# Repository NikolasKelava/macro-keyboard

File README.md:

# Macro Keyboard

A custom, wireless **Bluetooth LE macro keypad** with 12 mechanical keys, a magnetic rotary
encoder, and a 128×64 OLED built on a Nordic **nRF52840** module and running
[**ZMK**](https://zmk.dev). Keys and profiles are configurable live over ZMK
Studio; the encoder is a per-profile knob (volume / vertical scroll / horizontal
scroll / browser tabs). Battery-powered (2000 mAh LiPo) with USB-C charging.

This project was submitted to the **Hack Club Horizons** program. Its progress is logged
in [JOURNAL.md](./JOURNAL.md). The admission is still pending.

---

## What is a macro keyboard?

A macro keyboard is a **Human Interface Device** (HID), which executes **macros** on a connected
host computer. In this sense, it functions like a conventional keyboard, serving as the 
interface between human input and a computer action.

The difference between a standard keyboard and a macro keyboard lies in their respective 
functionalities. A standard keyboard performs "normal" key bindings (e.g., numbers, letters,
and function buttons), while a macro keyboard performs macros. These can be media keys 
(e.g., volume up/down, skip title), open applications on the host computer or executing 
entire commands, performing actions that would otherwise require **multiple keystrokes on a 
standard keyboard**.

This makes it easier to navigate the operating system by **removing friction** between the user
and the host.

## What is my macro keyboard and what does it do?

**My macro keyboard has 12 macro keys, a rotary magnetic encoder, an OLED display, is battery 
powered and supports up to 7 profiles.**

The **macro assigned to each key** can be configured **per profile**. Depending on which profile is 
active, a key can have up to seven different functions. Consequently, we can perform up to **84
different actions** with our 12 keys.

The **encoder mode** can also be configured. It can act as a **scroll wheel** in both vertical and
horizontal direction, control the **volume** or switch between browser tabs on the host. These **modes 
are bound to each profile** and can be changed by assigning a key on a profile, that cycles through 
the modes of the encoder. When moving to the next keypad profile, the encoder mode changes to the 
active profile's encoder mode. Returning to the previous profile will revert the encoder mode to its 
previous state.

The **OLED display** shows the selected keypad profile, the battery capacity, the connection mode, and 
the encoder mode.

You can think of the keypad profiles as the **user layer** of the macro keypad. These profiles are 
called the "keymap", and they are the layers where the macro keyboard's functionality is configured. 
This user layer live directly on the macro keyboard, so the macros stay **the same even when changing 
host devices.** A **profile** button on the macro keyboard is used to switch between profiles.

You can **configure** the keymap and profiles in real time without recompiling or reflashing the keypad 
through [**ZMK Studio**](https://zmk.studio), a graphical user interface for ZMK keyboard firmware.

The macro keyboard connects as a keypad **via Bluetooth** or **USB**. Hosts are cross-platform (Windows, 
macOS, Linux, and iOS). The keypad can be paired with up to five hosts and conveniently switch 
between them via assigned keys on the keymap.

## Layout

## Demo & photos

### Demo video:

[Quick demo video on youtube](https://youtube.com/shorts/6OSJ7Yoke_U)
 
### Photos: 

## Hardware overview

| | |
|---|---|
| **MCU** | Raytac MDBT50Q-1MV2 (nRF52840 Module) |
| **Input** | 12-key matrix with mx switches (3 rows × 4 cols) + 1 profile button |
| **Encoder** | AMS AS5600 magnetic rotary encoder (over I2C) |
| **Display** | 128×64 SSD1306 OLED (over I2C, with 1 bpp) |
| **Power** | 2000 mAh LiPo, BQ24040 charger, USB-C |
| **Enclosure** | 3D printed |

## Firmware overview

The macro keyboard runs custom ZMK Firmware, configured and built over a local toolchain.
> "ZMK Firmware is an open source (MIT) keyboard firmware built on the Zephyr™ Project Real Time Operating System (RTOS)." ([Introduction to ZMK](https://zmk.dev/docs))

Full toolchain and architecture notes are in [firmware/CLAUDE.md](./firmware/CLAUDE.md).

## Repository layout

```
macro_keyboard/
├── README.md               ← you are here
├── JOURNAL.md              ← build devlog
├── assets/journal-assets/  ← images referenced from the journal
├── firmware/
│   ├── CLAUDE.md               full firmware architecture & build notes
│   ├── IMPLEMENTATION_PLAN.md  milestone-by-milestone history
│   ├── zmk-config/             ZMK config: custom board files, module, 
│   │                           AS5600 driver, behaviors
│   └── zmk                     ZMK submodule (ZMK version for my toolchain)
└── hardware/
    ├── BOM.csv          build BOM
    ├── BOM_PCB.csv      per-component board BOM (JLCPCB SMT + hand-soldered)
    ├── BUILD.md         full build and assembly guide to reproduce the macro keyboard
    ├── PCB/KiCad/Macro-Keyboard-v4/   schematic, board, Gerbers, KiCad design files
    └── CASE/                          3D-printed enclosure (Fusion + mesh exports)
```

## Bill of Materials

- **[hardware/BOM.csv](./hardware/BOM.csv)** — **Master/build cost BOM**:
  PCB fabrication, JLCPCB assembly (the parts JLC populates), shipping, the on-PCB parts I 
  solder myself (OLED, key switches, JST, SWD header), and all off-PCB parts (encoder bearing/
  magnet/knob, battery, keycaps, enclosure, screws) with the approximated cost per element.
  -> in the end: what it cost to build one unit of my macro keypad.
- **[hardware/BOM_PCB.csv](./hardware/BOM_PCB.csv)** — **PCB BOM**:
  every component that physically sits on the board; some of the parts, that need to be soldered
  onto the PCB, can't be soldered in the PCBA step, usually because those parts are to big. So I
  solder those manually. (e.g. key switches, OLED display, JST connector for LiPo)
- **[production/bom.csv](./hardware/PCB/KiCad/Macro-Keyboard-v4/production/bom.csv)** — **PCBA BOM**: 
  After manufacturing the PCB, its populated with the components in this BOM. 
  This step is the PCB assembly. Only the parts for this manufacturing step are in this 
  BOM. (e.g. nRf module, caps, resistors, usb port, etc.)

Part numbers are given only for parts that can't be substituted; common passives (resistors, 
capacitors) are specified by value/footprint and left flexible. Prices are only in `BOM.csv`.

**Per-unit cost caveat:** JLCPCB sells PCBs in quantities of at least 5. 
The per-unit total in BOM.csv is the amortized build cost, meaning that building one yourself will
cost more than the per-unit cost alone.

## Schematic, PCB & Gerbers

- **Schematic (PDF):** [Macro-Keyboard-v4.pdf](./hardware/PCB/KiCad/Macro-Keyboard-v4/Macro-Keyboard-v4.pdf)
- **KiCad source:** [hardware/PCB/KiCad/Macro-Keyboard-v4/](./hardware/PCB/KiCad/Macro-Keyboard-v4/)
- **Gerbers:** [production/Macro-Keyboard-v4.zip](./hardware/PCB/KiCad/Macro-Keyboard-v4/production/Macro-Keyboard-v4.zip)
- **SMT Assembly:** [`bom.csv` + `positions.csv`](./hardware/PCB/KiCad/Macro-Keyboard-v4/production/)
- **Case:** [hardware/CASE/](./hardware/CASE/) — Fusion source + the meshes exported for 3D printing

## Pinout

From the Macro-Keyboard-v4 schematic:

| Function | Net |
|---|---|
| Matrix columns | col0=P0.16, col1=P0.14, col2=P0.15, col3=P0.13 |
| Matrix rows | row0=P0.20, row1=P0.21, row2=P0.19 |
| I²C bus (OLED + AS5600) | SDA=P0.24, SCL=P0.25 |
| Profile button | P1.02 (diode to GND, polled) |
| Battery ADC | P0.04 (AIN2, ÷ voltage divider) |

## Firmware — build & flash

Full toolchain and architecture notes are in [firmware/CLAUDE.md](./firmware/CLAUDE.md).
In short (especially for reproducing the macro keyboard):

**Flashing:** I installed a Adafruit nRF52 bootloader on my board. With this bootloader I
can use UF2 drag and drop to flash the firmware by just double-tapping the reset button,
which mounts the keypad as a USB drive (`NRF52BOOT`), and then dragging `zmk.uf2` onto it - the build format for UF2 bootloaders. The board reflashes and reboots into the new firmware.

By default my pipeline will give both .hex and .uf2 build artifacts (that contain the
firmware) for flashing the macro keyboard. Flashing the .hex artifact over SWD with a 
debugger probe will work, but the macro keypad won't boot into the firmware!

This is because the UF2 bootloader sits right at the start of the flash partition. When 
flashing, the actual Zephyr firmware receives a place after the bootloader. It has an 
offset. The bootloader then points to the firmware when booting. When the keypad is in 
UF2 drag-and-drop mode (by double-tapping reset), the firmware after the bootloader in 
the partition is replaced. The cool thing I noticed is that the user-layer keymap won't 
be replaced because it's located farther away from the firmware. Therefore, you can 
update the firmware without losing your keymaps.

However, the defined offset for the bootloader will be applied to all artifacts when 
building the firmware. If no bootloader is installed on your macro keyboard and you flash 
via SWD, there won't be a bootloader to point to your firmware and boot it.

If you don't want to install a bootloader and want to flash the firmware directly with 
your debugger, read the section in [firmware/CLAUDE.md → Bootloader](../firmware/CLAUDE.md) "If the bootloader has to be removed".

**Build (from `firmware/zmk_toolchain/app`, ZMK toolchain):**

```bash
source /firmware/zmk_toolchain/.venv/bin/activate

west build -p -d build/macro_keyboard/m3 -b macro_keyboard -- \
  -DZMK_CONFIG="$PWD/../../zmk-config/config" \
  -DZMK_EXTRA_MODULES="$PWD/../../zmk-config/module"
```

Add `-S studio-rpc-usb-uart -DCONFIG_ZMK_STUDIO=y` for the ZMK Studio variant.
The build emits both `zmk.uf2` (drag-drop) and `zmk.hex` (SWD via `west flash -r pyocd`).

Before doing so: Follow the official [ZMK firmware document](https://zmk.dev/docs/development/local-toolchain/setup) on setting up the local Zephyr toolchain to build the ZMK firmware with macro_keyboard config. Install the current version of ZMK, which is added as a submodule to this repo. Install under the path `firmware/zmk_toolchain/`.

## Steps to reproduce

Full instructions: **[hardware/BUILD.md](./hardware/BUILD.md)**.

## Safety notes

- **LiPo battery (2000 mAh):** observe correct polarity; do not puncture, crush, or short. Charge
  only through the on-board **BQ24040** charger via USB-C. Disconnect and isolate a swollen or 
  damaged cell — do not charge it.
- The board periphere is **3.3 V** logic; do not back-feed 5 V into signal pins.
- Powered by USB-C — use a compliant cable/supply.

## AI disclosure

Firmware:
I used Claude Code when developing the firmware. It helped me with tasks such as setting up the ZMK 
firmware, configuring my custom board, writing additional modules for the OLED display and a AS5600 
driver, and behaviors. Especially for debugging, I used Claude Code.
Although it may sound like I completely handed over the firmware work to Claude, in a sense, this is
true. However, I am obviously deeply involved in the development and manage it. Claude's role is to 
speed up the process by taking over tedious tasks and also giving me good overviews on how things 
can be implemented.
I did the research on the available firmware choices and how to design the hardware around them.

Hardware:
The hardware portion of the project, which is the largest part of the project, was completely done 
without the use of an LLM or any other AI.

Anything that Hackclub specifically prohibited the use of AI for was done without it (e.g. this README.md).

## License

| Part | License | File |
|---|---|---|
| Firmware, ZMK config, scripts, docs (everything outside `hardware/`) | **MIT** | [LICENSE](./LICENSE) |
| Hardware design — KiCad schematic/PCB, Gerbers, CAD/case, BOMs (everything in `hardware/`) | **CERN-OHL-S v2** | [hardware/LICENSE](./hardware/LICENSE) |

If you reuse the hardware design, keep a notice like this with it:

```
Copyright (c) 2026 Nikolas Kelava
This source describes Open Hardware and is licensed under CERN-OHL-S v2.
You may redistribute and modify this source and make products using it under
the terms of CERN-OHL-S v2 (https://ohwr.org/cern_ohl_s_v2.txt).
This source is distributed WITHOUT ANY EXPRESS OR IMPLIED WARRANTY, INCLUDING
OF MERCHANTABILITY, SATISFACTORY QUALITY AND FITNESS FOR A PARTICULAR PURPOSE.
Please see the CERN-OHL-S v2 for applicable conditions.
Source location: https://github.com/NikolasKelava/macro-keyboard
```

Third-party code keeps its own license: [ZMK](https://github.com/zmkfirmware/zmk)
is MIT, the [Zephyr RTOS](https://github.com/zephyrproject-rtos/zephyr) is
Apache-2.0, and the [Adafruit nRF52 bootloader](https://github.com/adafruit/Adafruit_nRF52_Bootloader)
in `firmware/bootloader/` is MIT.

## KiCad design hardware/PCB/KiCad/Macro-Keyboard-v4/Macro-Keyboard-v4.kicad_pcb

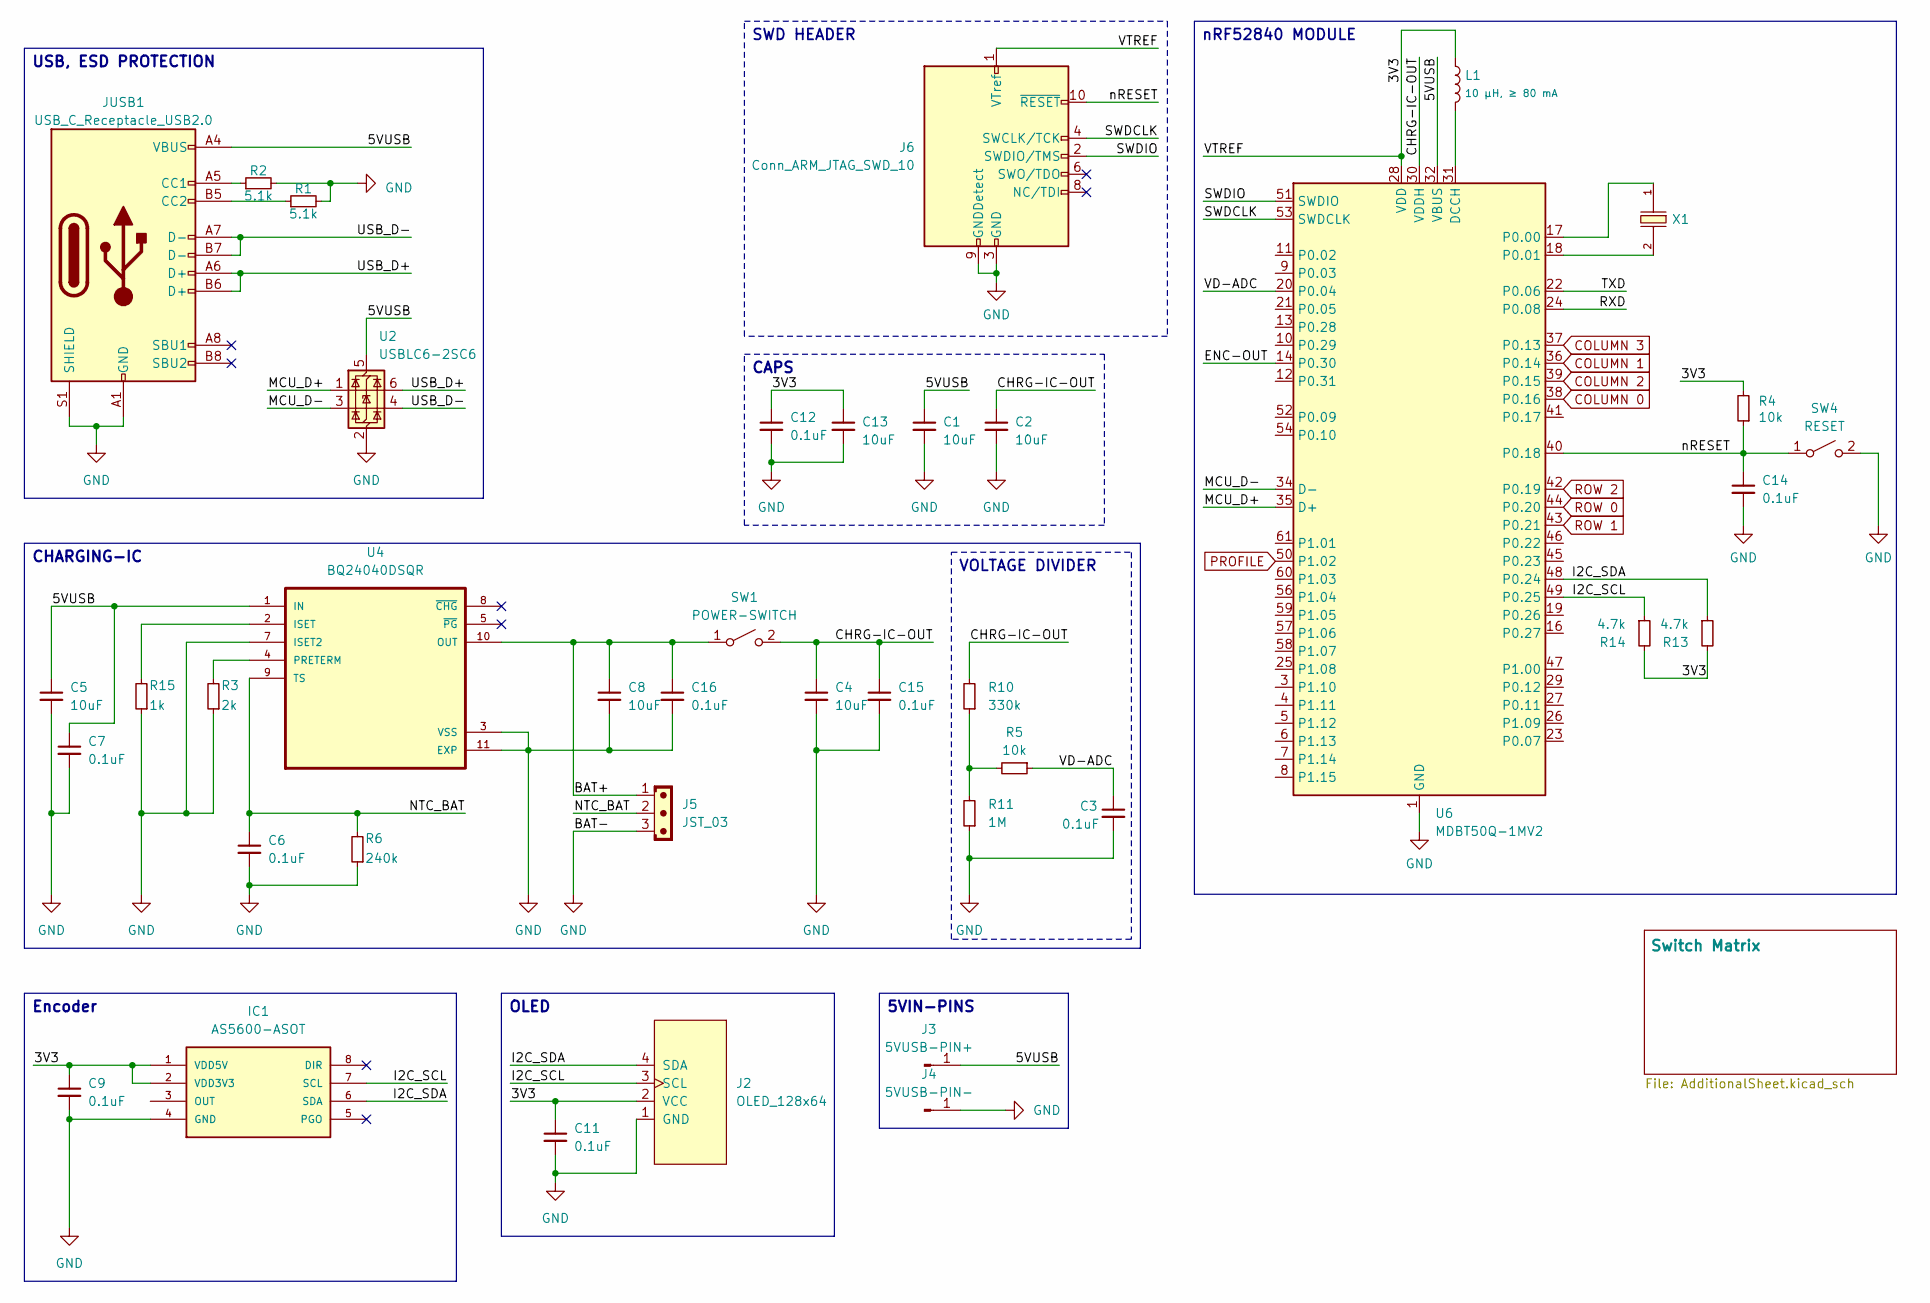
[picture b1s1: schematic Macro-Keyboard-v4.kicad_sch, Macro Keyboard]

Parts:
C1, C2, C4, C5, C8, C13: 10uF; C_0603_1608Metric
C3, C6, C7, C9, C11, C12, C14, C15, C16: 0.1uF; C_0603_1608Metric
IC1: AS5600-ASOT; SOIC127P600X175-8N; MOUSER_PART_NUMBER 985-AS5600-ASOT
J2: OLED_128x64
J3: 5VUSB-PIN+; BatteryPad
J4: 5VUSB-PIN-; BatteryPad
J5: JST_03; JST_XH_B3B-XH-AM_1x03_P2.50mm_Vertical
J6: Conn_ARM_JTAG_SWD_10; PinHeader_2x05_P1.27mm_Vertical
JUSB1: USB_C_Receptacle_USB2.0; USB_C_Receptacle_GCT_USB4105-xx-A_16P_TopMnt_Horizontal
L1: 10 µH, ≥ 80 mA; L_TDK_MLZ1608
R1, R2: 5.1k; R_0603_1608Metric
R3: 2k; R_0603_1608Metric
R4, R5: 10k; R_0603_1608Metric
R6: 240k; R_0603_1608Metric
R10: 330k; R_0603_1608Metric
R11: 1M; R_0603_1608Metric
R13, R14: 4.7k; R_0603_1608Metric
R15: 1k; R_0603_1608Metric
SW1: POWER-SWITCH; SW_SPDT_PCM12
SW4: RESET; SW_SPST_B3U-1000P; LCSC C720477
U2: USBLC6-2SC6; ESD_SOT-23-6; LCSC C2827654
U4: BQ24040DSQR; SON40P200X200X80-11N
U6: MDBT50Q-1MV2; Raytac_MDBT50Q
X1: Q13FC1350000400; FC-135R_L3.2-W1.5; Frequency Tolerance ±20ppm; Part Q13FC13500004; LCSC C32346

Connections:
/3V3: C9.1, C11.1, C12.1, C13.1, IC1.1 (VDD5V), IC1.2 (VDD3V3), J2.2 (VCC), J6.1 (VTref), L1.1, R4.2, R13.2, R14.2, U6.28 (VDD)
/5VUSB: C1.1, C5.1, C7.1, J3.1, JUSB1.A4 (VBUS), JUSB1.A9 (VBUS), JUSB1.B4 (VBUS), JUSB1.B9 (VBUS), U2.5 (VBUS), U4.1 (IN), U6.32 (VBUS)
/BAT+: C8.1, C16.1, J5.1, SW1.1 (A), U4.10 (OUT)
/CHRG-IC-OUT: C2.1, C4.1, C15.1, R10.2, SW1.2 (B), U6.30 (VDDH)
/ENC-OUT: U6.14 (P0.30)
/I2C_SCL: IC1.7 (SCL), J2.3 (SCL), R14.1, U6.49 (P0.25)
/I2C_SDA: IC1.6 (SDA), J2.4 (SDA), R13.1, U6.48 (P0.24)
/MCU_D+: U2.1 (I/O1), U6.35 (D+)
/MCU_D-: U2.3 (I/O2), U6.34 (D-)
/NTC_BAT: C6.1, J5.2, R6.2, U4.9 (TS)
/RXD: U6.24 (P0.08)
/SWDCLK: J6.4 (SWCLK/TCK), U6.53 (SWDCLK)
/SWDIO: J6.2 (SWDIO/TMS), U6.51 (SWDIO)
/TXD: U6.22 (P0.06)
/USB_D+: JUSB1.A6 (D+), JUSB1.B6 (D+), U2.6 (I/O1)
/USB_D-: JUSB1.A7 (D-), JUSB1.B7 (D-), U2.4 (I/O2)
/VD-ADC: C3.1, R5.1, U6.20 (P0.04)
/nRESET: C14.1, J6.10 (~RESET), R4.1, SW4.1 (A), U6.40 (P0.18)
COLUMN 0: U6.38 (P0.16); also elsewhere on the board
COLUMN 1: U6.36 (P0.14); also elsewhere on the board
COLUMN 2: U6.39 (P0.15); also elsewhere on the board
COLUMN 3: U6.37 (P0.13); also elsewhere on the board
GND: C1.2, C2.2, C3.2, C4.2, C5.2, C6.2, C7.2, C8.2, C9.2, C11.2, C12.2, C13.2, C14.2, C15.2, C16.2, IC1.4 (GND), J2.1 (GND), J4.1, J5.3, J6.3 (GND), J6.5 (GND), J6.9 (GNDDetect), JUSB1.A1 (GND), JUSB1.A12 (GND), JUSB1.B1 (GND), JUSB1.B12 (GND), JUSB1.S1 (SHIELD), R1.2, R2.2, R3.1, R6.1, R11.1, R15.1, SW4.2 (B), U2.2 (GND), U4.3 (VSS), U4.7 (ISET2), U4.11 (EXP), U6.1 (GND), U6.2 (GND), U6.15 (GND), U6.33 (GND), U6.55 (GND); also elsewhere on the board
unnamed: JUSB1.A5 (CC1), R2.1
unnamed: JUSB1.B5 (CC2), R1.1
unnamed: R5.2, R10.1, R11.2
unnamed: R15.2, U4.2 (ISET)
unnamed: R3.2, U4.4 (PRETERM)
unnamed: L1.2, U6.31 (DCCH)
unnamed: U6.17 (P0.00), X1.1
unnamed: U6.18 (P0.01), X1.2
PROFILE: U6.50 (P1.02); also elsewhere on the board
ROW 0: U6.44 (P0.20); also elsewhere on the board
ROW 1: U6.43 (P0.21); also elsewhere on the board
ROW 2: U6.42 (P0.19); also elsewhere on the board

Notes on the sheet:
OLED
USB, ESD PROTECTION
CAPS
SWD HEADER
Encoder
nRF52840 MODULE
5VIN-PINS
VOLTAGE DIVIDER
CHARGING-IC

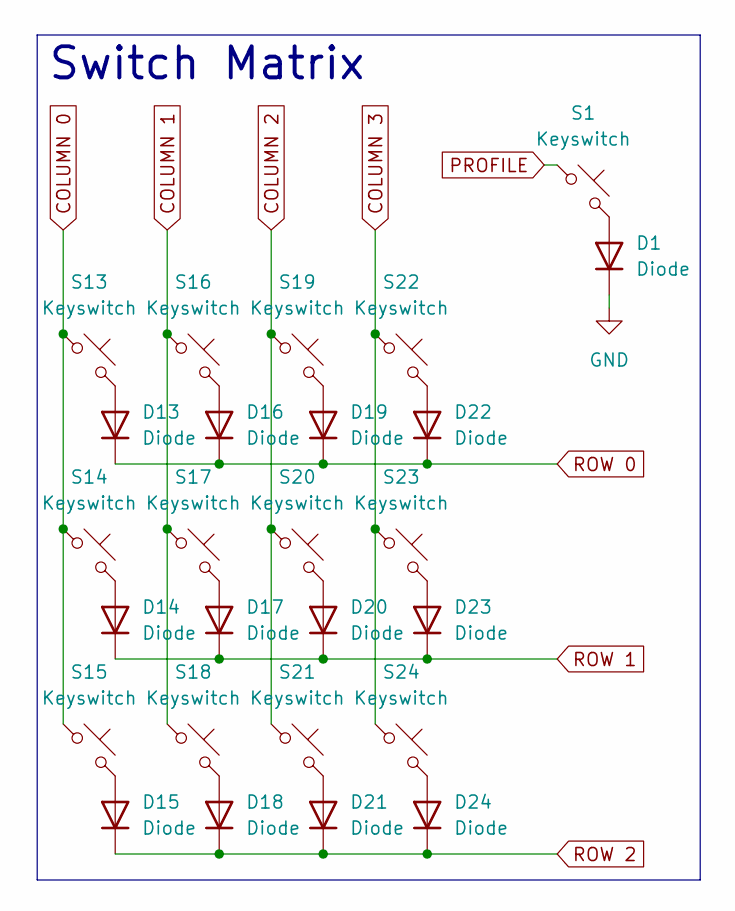
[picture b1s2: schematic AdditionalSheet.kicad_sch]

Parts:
D1, D13, D14, D15, D16, D17, D18, D19, D20, D21, D22, D23, D24: Diode; Diode_SOD-123
S1, S13, S14, S15, S16, S17, S18, S19, S20, S21, S22, S23, S24: Keyswitch; MX_PCB_1.00u

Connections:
COLUMN 0: S13.1, S14.1, S15.1; also elsewhere on the board
COLUMN 1: S16.1, S17.1, S18.1; also elsewhere on the board
COLUMN 2: S19.1, S20.1, S21.1; also elsewhere on the board
COLUMN 3: S22.1, S23.1, S24.1; also elsewhere on the board
GND: D1.1 (K); also elsewhere on the board
unnamed: D1.2 (A), S1.2
unnamed: D13.2 (A), S13.2
unnamed: D14.2 (A), S14.2
unnamed: D15.2 (A), S15.2
unnamed: D16.2 (A), S16.2
unnamed: D17.2 (A), S17.2
unnamed: D18.2 (A), S18.2
unnamed: D19.2 (A), S19.2
unnamed: D20.2 (A), S20.2
unnamed: D21.2 (A), S21.2
unnamed: D22.2 (A), S22.2
unnamed: D23.2 (A), S23.2
unnamed: D24.2 (A), S24.2
PROFILE: S1.1; also elsewhere on the board
ROW 0: D13.1 (K), D16.1 (K), D19.1 (K), D22.1 (K); also elsewhere on the board
ROW 1: D14.1 (K), D17.1 (K), D20.1 (K), D23.1 (K); also elsewhere on the board
ROW 2: D15.1 (K), D18.1 (K), D21.1 (K), D24.1 (K); also elsewhere on the board

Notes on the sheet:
Switch Matrix

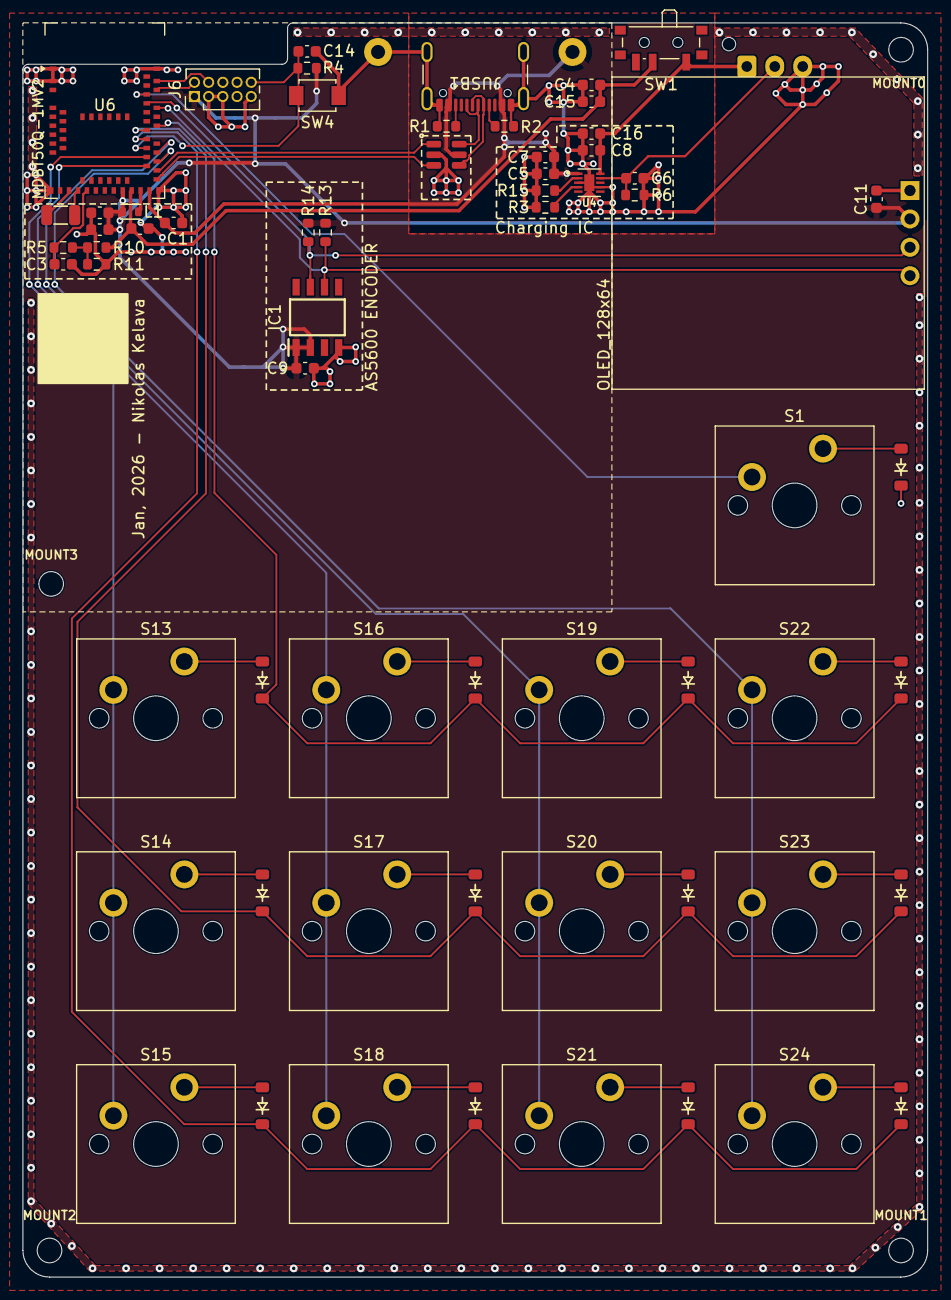
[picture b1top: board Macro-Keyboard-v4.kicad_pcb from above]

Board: 4 copper layers, 81.0 x 112.2 mm, 70 parts (1 on the bottom side), 45 nets.

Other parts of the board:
MOUNT0, MOUNT1, MOUNT2, MOUNT3: MountingHole_2.2mm_M2

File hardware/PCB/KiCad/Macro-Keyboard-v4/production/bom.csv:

Designator,Footprint,Quantity,Value,LCSC Part #
"C1, C13, C2, C4, C5, C8",0603,6,10uF,
"C11, C12, C14, C15, C16, C3, C6, C7, C9",0603,9,0.1uF,
"D1, D13, D14, D15, D16, D17, D18, D19, D20, D21, D22, D23, D24",Diode_SOD-123,13,Diode,C81598
IC1,SOIC127P600X175-8N,1,AS5600-ASOT,C79815
J5,JST_XH_B3B-XH-AM_1x03_P2.50mm_Vertical,1,JST_03,
J6,PinHeader_2x05_P1.27mm_Vertical,1,Conn_ARM_JTAG_SWD_10,
JUSB1,USB_C_Receptacle_GCT_USB4105-xx-A_16P_TopMnt_Horizontal,1,USB_C_Receptacle_USB2.0,C165948
L1,L_TDK_MLZ1608,1,"10 µH, ≥ 80 mA",
"R1, R2",0603,2,5.1k,
R10,0603,1,330k,
R11,0603,1,1M,
"R13, R14",0603,2,4.7k,
R15,0603,1,1k,
R3,0603,1,2k,
"R4, R5",0603,2,10k,
R6,0603,1,240k,
"S1, S13, S14, S15, S16, S17, S18, S19, S20, S21, S22, S23, S24",MX_PCB_1.00u,13,Keyswitch,
SW1,SW_SPDT_PCM12,1,POWER-SWITCH,
SW4,SW_SPST_B3U-1000P,1,RESET,C720477
U2,ESD_SOT-23-6,1,USBLC6-2SC6,C2827654
U4,SON40P200X200X80-11N,1,BQ24040DSQR,
U6,Raytac_MDBT50Q,1,MDBT50Q-1MV2,
X1,FC-135R_L3.2-W1.5,1,Q13FC1350000400,C32346

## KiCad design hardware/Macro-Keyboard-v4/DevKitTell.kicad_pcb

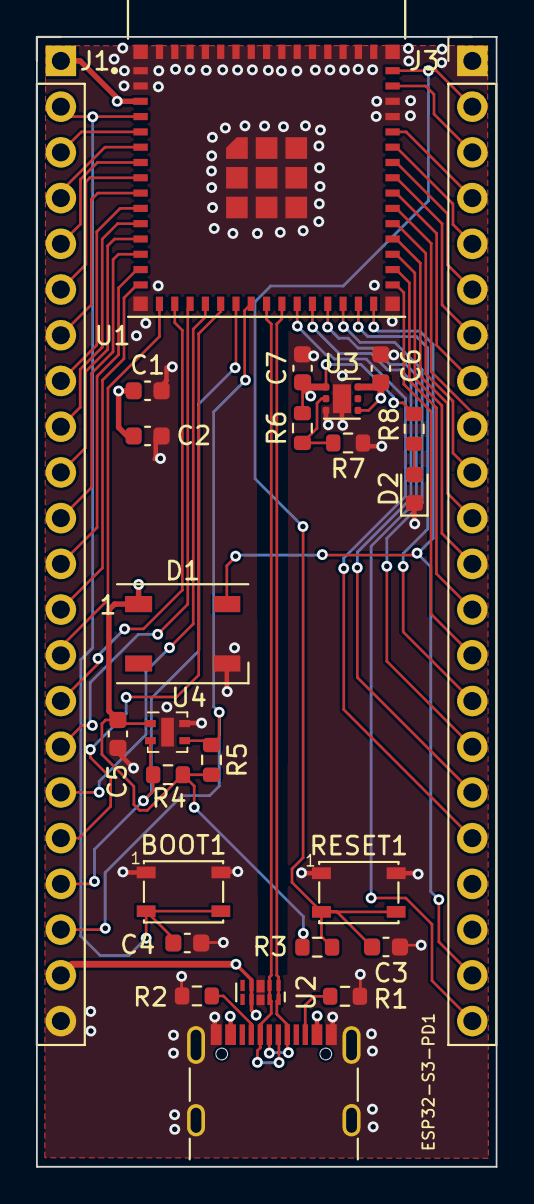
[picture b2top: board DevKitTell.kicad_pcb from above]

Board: 4 copper layers, 25.5 x 62.8 mm, 26 parts (0 on the bottom side), 47 nets.

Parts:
BOOT1: SW_SPST_PTS810
C1, C3, C4, C5: 0.1uF; C_0603_1608Metric
C2, C6, C7: 10uF; C_0603_1608Metric
D1: WS2812B; LED_WS2812B_PLCC4_5.0x5.0mm_P3.2mm
D2: LED; LED_0603_1608Metric
J1, J3: PinHeader_1x22_P2.54mm_Vertical
JUSB1: USB_C_Receptacle_USB2.0; USB_C_Receptacle_GCT_USB4105-xx-A_16P_TopMnt_Horizontal
R1, R2, R8: 5.1k; R_0603_1608Metric
R3, R4, R5: 10k; R_0603_1608Metric
R6: 1M; R_0603_1608Metric
R7: 200k; R_0603_1608Metric
RESET1: SW_SPST_PTS810
U1: ESP32-S3-MINI-1-N8; XCVR_ESP32-S3-MINI-1-N8
U2: D3V3XA4B10LP; Diodes_UDFN-10_1.0x2.5mm_P0.5mm
U3: TLV75801PDRV; WSON-6-1EP_2x2mm_P0.65mm_EP1x1.6mm
U4: ENS210; AMS_QFN-4-1EP_2x2mm_P0.95mm_EP0.7x1.6mm

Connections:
/3V3: C1.1, C2.1, C5.1, C7.1, D1.1 (VDD), J1.1, R3.2, R4.2, R5.2, R6.2, R8.1, U1.3 (3V3), U3.1 (OUT), U4.1 (VDD)
/5VUSB: C6.1, J1.21, JUSB1.A4 (VBUS), JUSB1.A9 (VBUS), JUSB1.B4 (VBUS), JUSB1.B9 (VBUS), U2.4, U2.7 (NC), U3.4 (EN), U3.6 (IN)
/ESP32_EN: C3.1, J3.2, R3.1, RESET1.3 (K), RESET1.4 (A), U1.45 (EN)
/GPIO0: BOOT1.3 (K), BOOT1.4 (A), C4.1, J1.2, U1.4 (IO0)
/GPIO1: J1.3, U1.5 (IO1)
/GPIO2: J1.4, U1.6 (IO2)
/GPIO3: J1.5, U1.7 (IO3)
/GPIO4: J1.6, U1.8 (IO4)
/GPIO5: J1.7, U1.9 (IO5)
/GPIO6: J1.8, U1.10 (IO6)
/GPIO7: J1.9, U1.11 (IO7)
/GPIO8: J1.10, U1.12 (IO8)
/GPIO9: J1.11, U1.13 (IO9)
/GPIO10: J1.12, U1.14 (IO10)
/GPIO11: J1.13, U1.15 (IO11)
/GPIO12: J1.14, U1.16 (IO12)
/GPIO13: J1.15, U1.17 (IO13)
/GPIO14: J1.16, U1.18 (IO14)
/GPIO15: J1.17, U1.19 (IO15)
/GPIO16: J1.18, U1.20 (IO16)
/GPIO21: J3.18, U1.25 (IO21)
/GPIO26: J3.17, U1.26 (IO26)
/GPIO33: J3.16, U1.28 (IO33)
/GPIO34: J3.15, U1.29 (IO34)
/GPIO35: J3.14, U1.31 (IO35)
/GPIO36: J3.13, U1.32 (IO36)
/GPIO37: J3.12, U1.33 (IO37)
/GPIO38: J3.11, U1.34 (IO38)
/GPIO39: J3.10, U1.35 (IO39)
/GPIO40: J3.9, U1.36 (IO40)
/GPIO41: J3.8, U1.37 (IO41)
/GPIO42: J3.7, U1.38 (IO42)
/GPIO45: J3.4, U1.41 (IO45)
/GPIO46: J3.3, U1.44 (IO46)
/GPIO47: J3.22, U1.27 (IO47)
/GPIO48: D1.4 (DIN), J3.21, U1.30 (IO48)
/I2C_SCL: J1.19, R4.1, U1.21 (IO17), U4.2 (SCL)
/I2C_SDA: J1.20, R5.1, U1.22 (IO18), U4.3 (SDA)
/RXD: J3.5, U1.40 (RXD0)
/TXD: J3.6, U1.39 (TXD0)
/USB_N: JUSB1.A7 (D-), JUSB1.B7 (D-), U1.23 (IO19), U2.2, U2.9 (NC)
/USB_P: JUSB1.A6 (D+), JUSB1.B6 (D+), U1.24 (IO20), U2.1, U2.10 (NC)
GND: BOOT1.1, BOOT1.2, C1.2, C2.2, C3.2, C4.2, C5.2, C6.2, C7.2, D1.3 (VSS), D2.1 (K), J1.22, J3.1, JUSB1.A1 (GND), JUSB1.A12 (GND), JUSB1.B1 (GND), JUSB1.B12 (GND), JUSB1.S1 (SHIELD), R1.2, R2.2, R7.1, RESET1.1, RESET1.2, U1.1 (GND), U1.2 (GND), U1.42 (GND), U1.43 (GND), U1.46 (GND), U1.47 (GND), U1.48 (GND), U1.49 (GND), U1.50 (GND), U1.51 (GND), U1.52 (GND), U1.53 (GND), U1.54 (GND), U1.55 (GND), U1.56 (GND), U1.57 (GND), U1.58 (GND), U1.59 (GND), U1.60 (GND), U1.61 (GND), U1.61_1 (GND), U1.61_2 (GND), U1.61_3 (GND), U1.61_4 (GND), U1.61_5 (GND), U1.61_6 (GND), U1.61_7 (GND), U1.61_8 (GND), U1.62 (GND), U1.63 (GND), U1.64 (GND), U1.65 (GND), U2.3 (VSS), U2.8 (VSS), U3.3 (GND), U3.7 (GND), U4.4 (GND), U4.5 (GND)
unnamed: D2.2 (A), R8.2
unnamed: JUSB1.A5 (CC1), R2.1
unnamed: JUSB1.B5 (CC2), R1.1
unnamed: R6.1, R7.2, U3.2 (FB)

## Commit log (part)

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2026-02-07 Initial commit: Project structure and hardware files
2026-02-08 macro_keyboard config
2026-02-08 Test authentication
2026-02-08 deleting README
2026-02-14 Adding Hardware Files
2026-02-14 Creating development folder
2026-02-19 Minimal Board Config
    Adding the minimal required board files so Zephyr recognizes the board, including ZMK-Studio support and a cursorrules file
2026-02-19 Adding missing features
    Profile system: adding 4 profiles as layers and a dedicated profile switch button to cycle between the profiles, OLED enablement: turn on I2C OLED support and integrate display updates for battery + 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
2026-02-19 Restructuring hardware folders
2026-04-12 Revert board config
    Board config had fundamental problems. Deleting them in order to completely start from scratch.
2026-04-13 Milestone 1: Create minimal board config
2026-05-06 Milestone 1: Flash partition layout (fixed)
2026-05-06 Milestone 2: Activate UI + sensors
2026-05-14 Milestone 3: Profiles
    Additionally redefined the Milestones
2026-05-28 Milestone 4: BUILT_IN screen
2026-05-31 Milestone 4: Custom screen
2026-05-31 Cosmetics Screen (Battery icon + layout)
2026-06-08 Milestone 5: AS5600 Encoder (+smooth scrolling without acceleration)
    + fixed the overheating issue of the mac when flashing the board via uf2
2026-06-08 Milestone 5: Encoder documentation
2026-06-21 Milestone 5: Adding high res scrolling + tab mode + usb hang fix (root cause)
2026-06-21 Format CLAUDE.md
